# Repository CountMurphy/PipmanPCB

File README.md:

# PipmanPCB
This repo has been deprecated. The current board files have been ported to kicad and are in the main repo. https://github.com/CountMurphy/Pipman

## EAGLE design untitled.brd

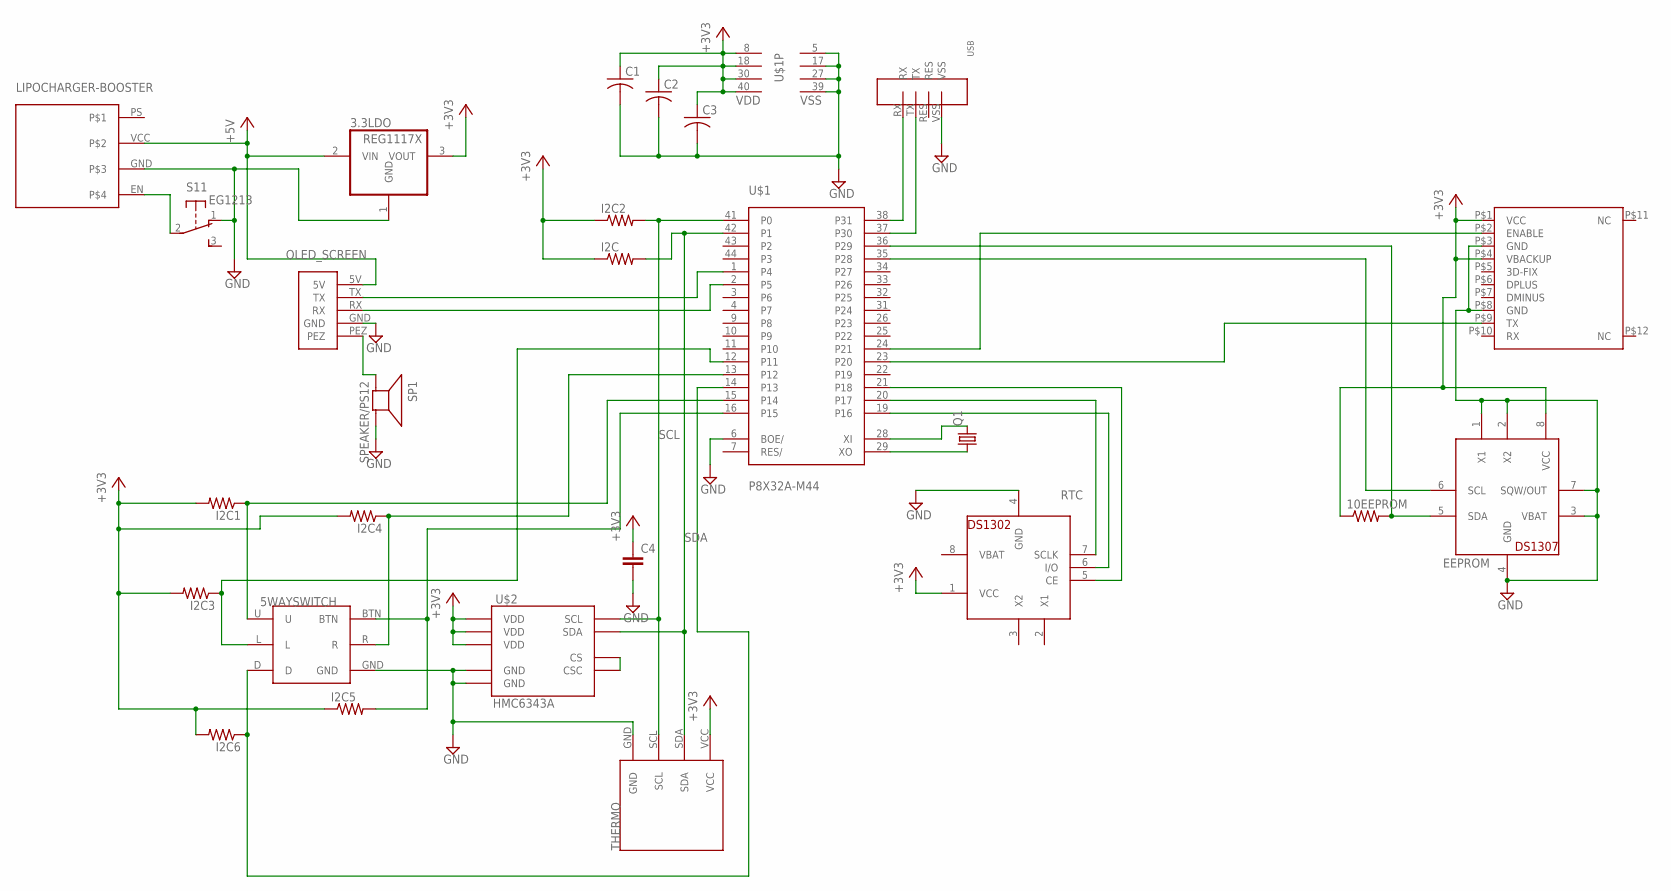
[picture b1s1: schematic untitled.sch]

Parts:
3.3LDO: REG1117X; TO252
5WAYSWITCH: 5-WAYSWITCH
10EEPROM: R-US_R1005; R1005
C1, C2, C3: C-USC0603; C0603
C4: CAP0603; 0603
EEPROM: DS1307; DIL08
GPS: GPS_FGPMMOPA6B; FGPMMOPA6B
I2C, I2C1, I2C2, I2C3, I2C4, I2C5, I2C6: R-US_R1005; R1005
LIPOCHARGER-BOOSTER: SFLIPO
OLED_SCREEN: 4DSCREEN
Q1: CRYSTALHC49S; HC49/S
RTC: DS1302; DIL08-ROUND
S1: EG1213
SP1: SPEAKER/PS12; PS12
THERMO: SFTEMP
U$1: P8X32A-M44
U$2: HMC6343A; LCC36
USB: 4PINUSB

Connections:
+3V3: 3.3LDO.3 (VOUT), 10EEPROM.1, C1.1, C2.1, C3.1, C4.1, EEPROM.8 (VCC), GPS.P$1 (VCC), GPS.P$4 (VBACKUP), I2C.1, I2C1.2, I2C2.1, I2C3.2, I2C4.2, I2C5.1, I2C6.2, RTC.1 (VCC), THERMO.VCC, U$1.8 (VDD), U$1.18 (VDD), U$1.30 (VDD), U$1.40 (VDD), U$2.3 (VDD), U$2.11 (VDD), U$2.21 (VDD)
+5V: 3.3LDO.2 (VIN), LIPOCHARGER-BOOSTER.VCC, OLED_SCREEN.5V
GND: 3.3LDO.1 (GND), 5WAYSWITCH.GND, C1.2, C2.2, C3.2, C4.2, EEPROM.1 (X1), EEPROM.2 (X2), EEPROM.3 (VBAT), EEPROM.4 (GND), EEPROM.7 (SQW/OUT), GPS.P$3 (GND), GPS.P$8 (GND), LIPOCHARGER-BOOSTER.GND, OLED_SCREEN.GND, RTC.4 (GND), S1.1 (O), SP1.P$2 (-), THERMO.GND, U$1.5 (VSS), U$1.6 (BOE/), U$1.17 (VSS), U$1.27 (VSS), U$1.39 (VSS), U$2.25 (GND), U$2.29 (GND), USB.VSS
unnamed: Q1.2, U$1.28 (XI)
unnamed: Q1.1, U$1.29 (XO)
unnamed: GPS.P$9 (TX), U$1.23 (P20)
unnamed: GPS.P$2 (ENABLE), U$1.24 (P21)
unnamed: RTC.5 (CE), U$1.21 (P18)
unnamed: RTC.6 (I/O), U$1.19 (P16)
unnamed: U$1.38 (P31), USB.RX
unnamed: RTC.7 (SCLK), U$1.20 (P17)
unnamed: U$1.37 (P30), USB.TX
unnamed: OLED_SCREEN.RX, U$1.2 (P5)
unnamed: OLED_SCREEN.TX, U$1.1 (P4)
unnamed: OLED_SCREEN.PEZ, SP1.P$1 (+)
unnamed: LIPOCHARGER-BOOSTER.EN, S1.2
unnamed: 5WAYSWITCH.U, I2C1.1, U$1.15 (P14)
unnamed: 5WAYSWITCH.D, I2C6.1, U$1.14 (P13)
unnamed: 5WAYSWITCH.L, I2C3.1, U$1.12 (P11)
unnamed: 10EEPROM.2, EEPROM.5 (SDA), U$1.36 (P29)
unnamed: EEPROM.6 (SCL), U$1.35 (P28)
unnamed: 5WAYSWITCH.R, I2C4.1, U$1.13 (P12)
unnamed: 5WAYSWITCH.BTN, I2C5.2, U$1.16 (P15)
unnamed: U$2.22 (CS), U$2.35 (CSC)
SCL: I2C2.2, THERMO.SCL, U$1.41 (P0), U$2.32 (SCL)
SDA: I2C.2, THERMO.SDA, U$1.42 (P1), U$2.36 (SDA)
VBAT: RTC.8 (VBAT)

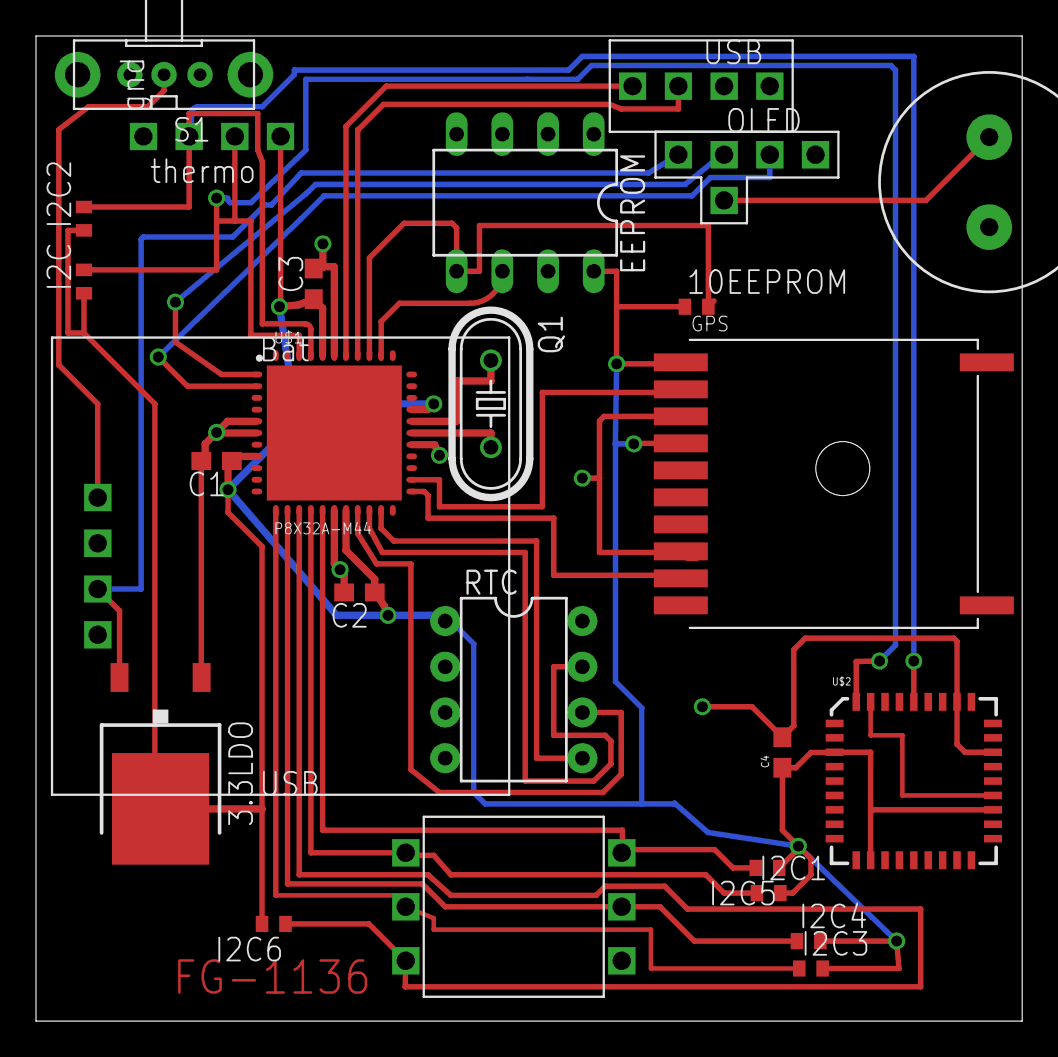
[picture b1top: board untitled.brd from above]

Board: 2 copper layers, 54.8 x 54.7 mm, 26 parts (0 on the bottom side), 26 nets.

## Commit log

2014-10-28 Shrunk board form factor
2014-10-28 Made correction in hole size for through hole components
2014-10-28 added cyberdyne logo
2014-11-08 fixed stupid and costly mistake with screen position
2014-11-08 moved eeprom
2014-11-09 fixed silly trace
2014-11-10 added optional speaker
2014-11-10 moved switch resistors to better fit 3d case.
2014-11-11 fixed bad cap trace
2014-11-30 removed airwire in power switch, fixed reversal of screen pins and verified ALL other parts. Nice going genius
